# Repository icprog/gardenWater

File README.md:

# gardenWater

###What is this?

This project is for the lazy men in you, it will simply use an Adafruit HUZZAH to drive two water valves to control the watering of the backyard garden and tomatoes plants. It will be controlled from a web page using the aREST API for the ESP8266.

Web page will probably be hosted on a RaspberryPi2 I already have running for other stuff.

###Hardware
- Adafruit HUZZAH
- 2x Solenoid water 1/2" valves

###Libraries used
- aREST

###IDE
- PlatformIO [http://platformio.org/](http://platformio.org/)

###Things to come
- Pictures
- Currently waiting for some parts to continue project.

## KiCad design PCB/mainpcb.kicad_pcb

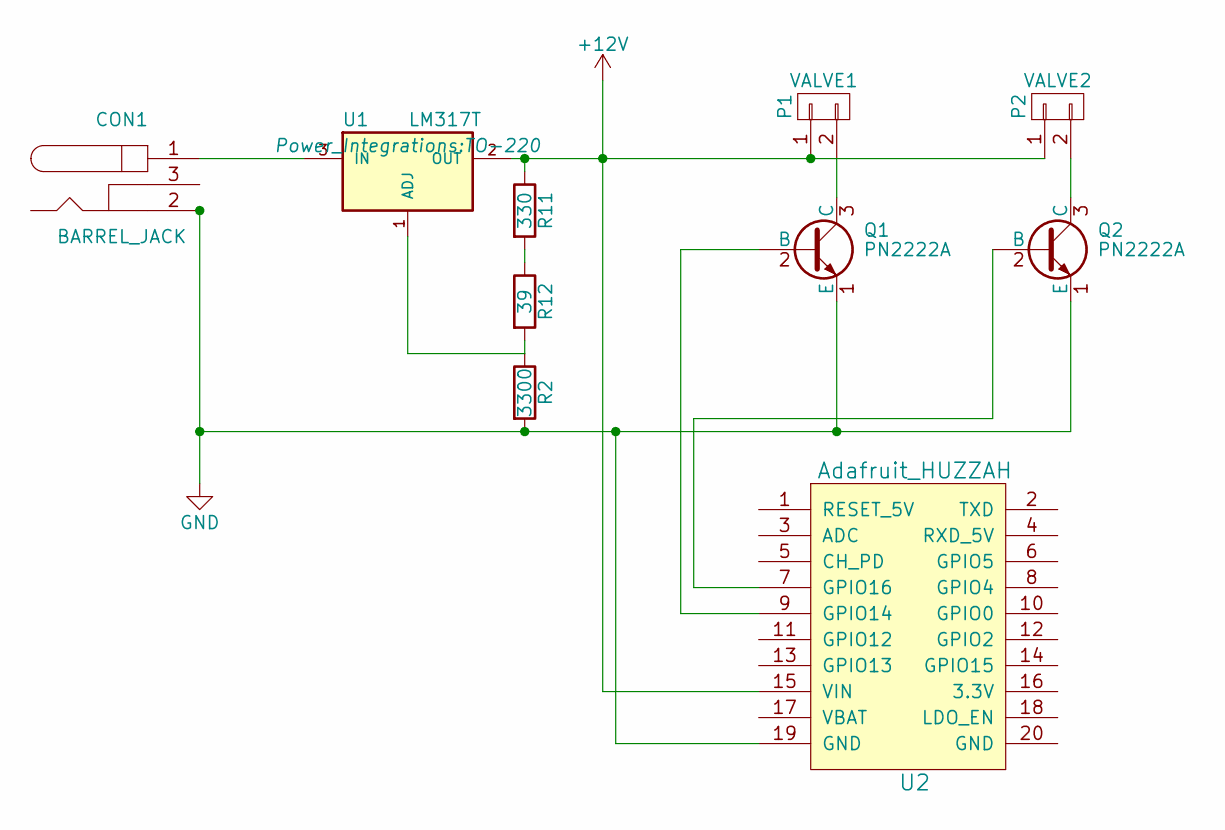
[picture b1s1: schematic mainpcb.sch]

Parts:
CON1: BARREL_JACK
P1: VALVE1; Pin_Header_Straight_1x02
P2: VALVE2; Pin_Header_Straight_1x02
Q1, Q2: PN2222A; TO-92_Inline_Narrow_Oval
R2: 3300; Resistor_Horizontal_RM7mm
R11: 330; Resistor_Horizontal_RM7mm
R12: 39; Resistor_Horizontal_RM7mm
U1: LM317T; TO-220
U2: Adafruit_HUZZAH; Adafruit-HUZZAH

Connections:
+12V: P1.1, P2.1, R11.1, U1.2 (OUT), U2.15 (VIN)
GND: CON1.2, Q1.1 (E), Q2.1 (E), R2.2, U2.19 (GND)
unnamed: CON1.1, U1.3 (IN)
unnamed: P1.2, Q1.3 (C)
unnamed: P2.2, Q2.3 (C)
unnamed: Q1.2 (B), U2.9 (GPIO14)
unnamed: Q2.2 (B), U2.7 (GPIO16)
unnamed: R11.2, R12.1
unnamed: R2.1, R12.2, U1.1 (ADJ)

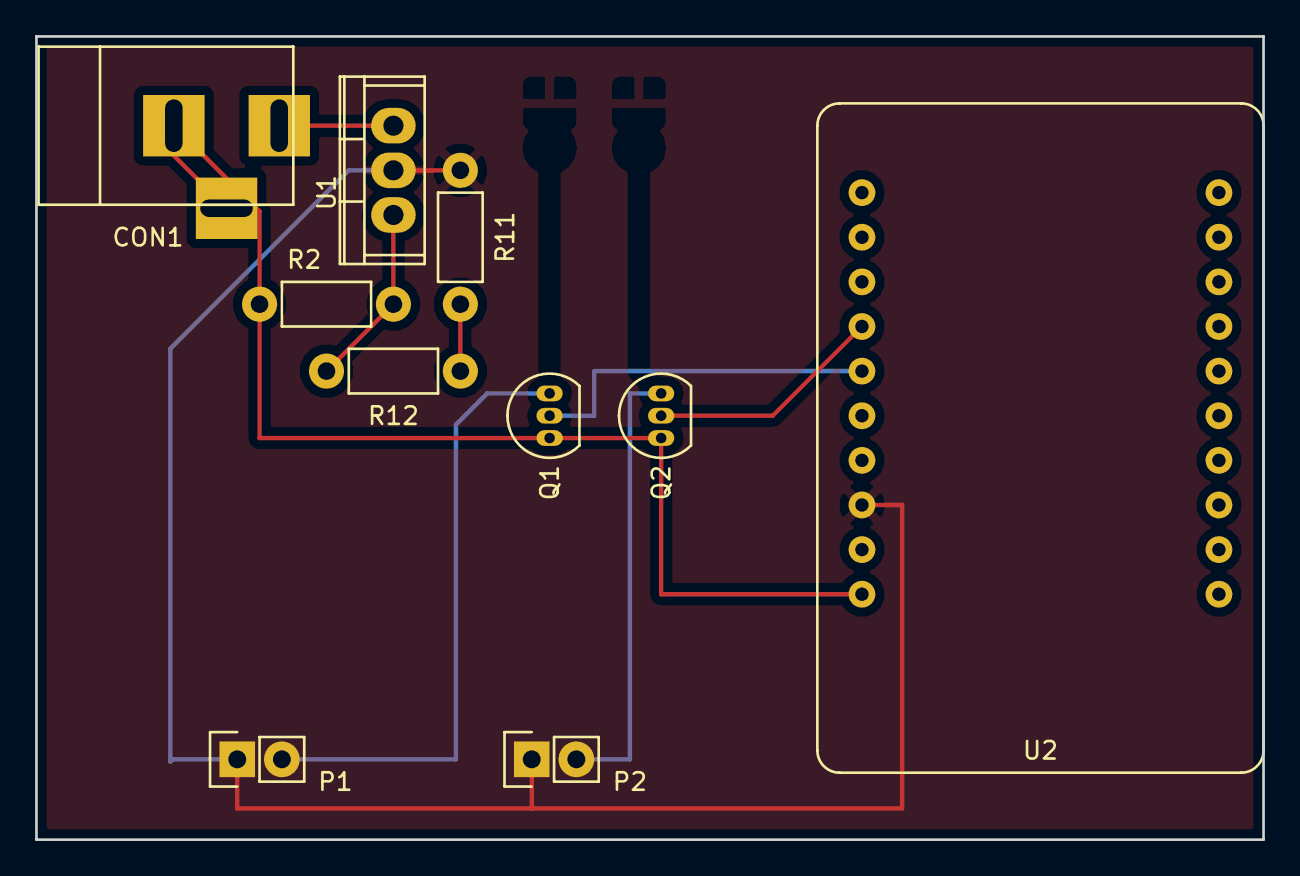
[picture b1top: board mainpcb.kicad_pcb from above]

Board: 2 copper layers, 69.8 x 45.7 mm, 10 parts (0 on the bottom side), 9 nets.

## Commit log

2016-03-27 :confetti_ball: Added .gitattributes
2016-03-27 initial upload
2016-03-29 power and ground plane
2016-03-30 structure changes
2016-03-30 structure again
2016-03-31 Test commit from Atom
2016-03-31 test
2016-04-23 pcb changes
